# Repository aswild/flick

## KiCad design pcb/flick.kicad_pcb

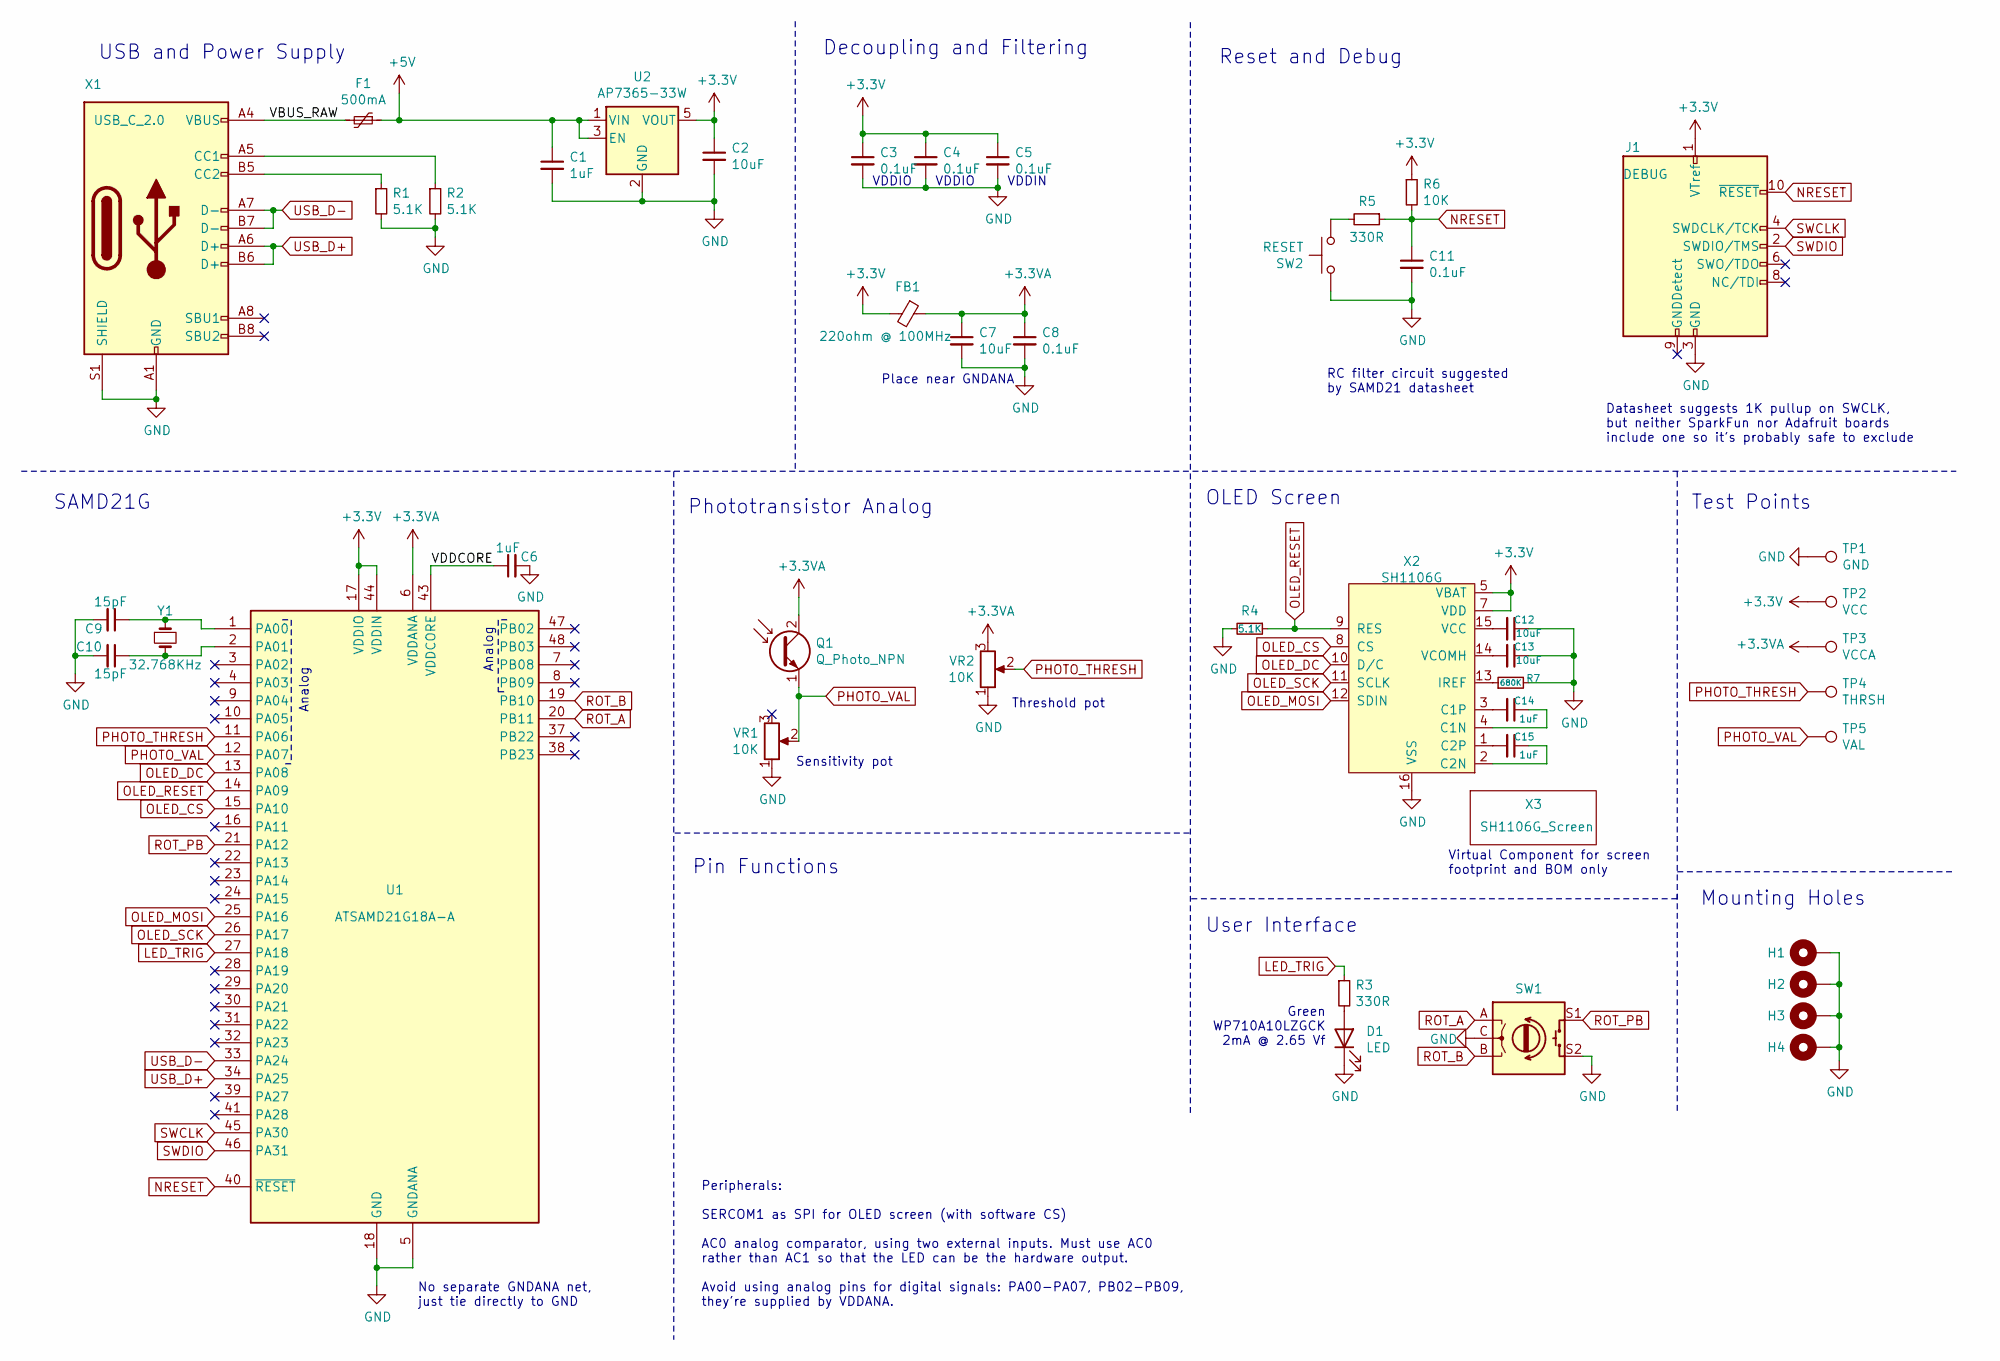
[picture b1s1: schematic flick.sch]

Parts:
C1, C6, C14, C15: 1uF; C_0805_2012Metric_Pad1.18x1.45mm_HandSolder; DigiKey PN 1276-1026-1-ND
C2, C7, C12, C13: 10uF; C_0805_2012Metric_Pad1.18x1.45mm_HandSolder; DigiKey PN 1276-2893-1-ND
C3, C4, C5, C8, C11: 0.1uF; C_0603_1608Metric_Pad1.08x0.95mm_HandSolder; DigiKey PN 1276-1935-1-ND
C9, C10: 15pF; C_0603_1608Metric_Pad1.08x0.95mm_HandSolder; DigiKey PN 1292-1487-1-ND
D1: LED; LED_D3.0mm; DigiKey PN 754-1915-ND
F1: 500mA; Fuse_1206_3216Metric_Pad1.42x1.75mm_HandSolder; DigiKey PN 507-1800-1-ND
FB1: 220ohm @ 100MHz; L_0805_2012Metric_Pad1.05x1.20mm_HandSolder; DigiKey PN A103650CT-ND
H1, H2, H3, H4: MountingHole_Pad; MountingHole_5mm_Pad
J1: DEBUG; PinHeader_2x05_P1.27mm_Vertical_SMD; DigiKey PN S9012E-05-ND
Q1: Q_Photo_NPN; LED_D5.0mm; DigiKey PN 1528-2545-ND
R1, R2, R4: 5.1K; R_0603_1608Metric_Pad0.98x0.95mm_HandSolder; DigiKey PN RMCF0603FT5K10CT-ND
R3, R5: 330R; R_0805_2012Metric_Pad1.20x1.40mm_HandSolder; DigiKey PN RMCF0805FT330RCT-ND
R6: 10K; R_0805_2012Metric_Pad1.20x1.40mm_HandSolder; DigiKey PN RMCF0805FT10K0CT-ND
R7: 680K; R_0603_1608Metric_Pad0.98x0.95mm_HandSolder; DigiKey PN RMCF0603FT680KCT-ND
SW1: Rotary_Encoder_Switch; RotaryEncoder_Bourns_PEC11L-Switch_Vertical_H20mm; DigiKey PN 118-PEC11L-4120K-S0020-ND
SW2: RESET; SW_SPST_PTS645; DigiKey PN CKN11907CT-ND
TP1: GND; TestPoint_THTPad_D1.6mm_Drill1.0mm
TP2: VCC; TestPoint_THTPad_D1.6mm_Drill1.0mm
TP3: VCCA; TestPoint_THTPad_D1.6mm_Drill1.0mm
TP4: THRSH; TestPoint_THTPad_D1.6mm_Drill1.0mm
TP5: VAL; TestPoint_THTPad_D1.6mm_Drill1.0mm
U1: ATSAMD21G18A-A; TQFP-48_7x7mm_P0.5mm; DigiKey PN ATSAMD21G18A-AFTCT-ND
U2: AP7365-33W; SOT-23-5_HandSoldering; DigiKey PN AP7365-33WG-7DICT-ND
VR1, VR2: 10K; Potentiometer_Bourns_PTV09A-1_Single_Vertical; DigiKey PN PTV09A-4020S-B103-ND
X1: USB_C_2.0; USB_C_Receptacle_GCT_USB4105; DigiKey PN 2073-USB4105-GF-ACT-ND
X2: SH1106G; GCT_FFC2B28-16_1x16-1MP_P0.5mm_Horizontal; DigiKey PN 2073-FFC2B28-16-GCT-ND
X3: SH1106G_Screen; SH1106G_SCREEN; DigiKey PN 1528-5228-ND
Y1: 32.768KHz; Crystal_SMD_MicroCrystal_CC8V-T1A-2Pin_2.0x1.2mm_HandSolder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; DigiKey PN 2195-CM8V-T1A-32.768KHZ-12.5PF-20PPM-TA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

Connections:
+3.3VA: C7.1, C8.1, FB1.1, Q1.2 (C), TP3.1, U1.6 (VDDANA), VR2.3
+3V3: C2.1, C3.1, C4.1, C5.1, FB1.2, J1.1 (VTref), R6.1, TP2.1, U1.17 (VDDIO), U1.36 (VDDIO), U1.44 (VDDIN), U2.5 (VOUT), X2.5 (VBAT), X2.7 (VDD)
+5V: C1.1, F1.1, U2.1 (VIN), U2.3 (EN)
/VBUS_RAW: F1.2, X1.A4 (VBUS), X1.A9 (VBUS), X1.B4 (VBUS), X1.B9 (VBUS)
/VDDCORE: C6.1, U1.43 (VDDCORE)
GND: C1.2, C2.2, C3.2, C4.2, C5.2, C6.2, C7.2, C8.2, C9.2, C10.2, C11.2, C12.1, C13.1, D1.1 (K), H1.1, H2.1, H3.1, H4.1, J1.3 (GND), J1.5 (GND), R1.2, R2.2, R4.2, R7.2, SW1.C, SW1.S2, SW2.1, TP1.1, U1.5 (GNDANA), U1.18 (GND), U1.35 (GND), U1.42 (GND), U2.2 (GND), VR1.1, VR2.1, X1.A1 (GND), X1.A12 (GND), X1.B1 (GND), X1.B12 (GND), X1.S1 (SHIELD), X2.6 (VSS), X2.16 (VSS)
LED_TRIG: R3.1, U1.27 (PA18)
NRESET: C11.1, J1.10 (~RESET~), R5.1, R6.2, U1.40 (~RESET)
unnamed: C9.1, U1.1 (PA00), Y1.1
unnamed: C10.1, U1.2 (PA01), Y1.2
unnamed: C12.2, X2.15 (VCC)
unnamed: C13.2, X2.14 (VCOMH)
unnamed: C14.1, X2.4 (C1N)
unnamed: C14.2, X2.3 (C1P)
unnamed: C15.1, X2.2 (C2N)
unnamed: C15.2, X2.1 (C2P)
unnamed: D1.2 (A), R3.2
unnamed: R1.1, X1.B5 (CC2)
unnamed: R2.1, X1.A5 (CC1)
unnamed: R5.2, SW2.2
unnamed: R7.1, X2.13 (IREF)
OLED_CS: U1.15 (PA10), X2.8 (CS)
OLED_DC: U1.13 (PA08), X2.10 (D/C)
OLED_MOSI: U1.25 (PA16), X2.12 (SDIN)
OLED_RESET: R4.1, U1.14 (PA09), X2.9 (RES)
OLED_SCK: U1.26 (PA17), X2.11 (SCLK)
PHOTO_THRESH: TP4.1, U1.11 (PA06), VR2.2
PHOTO_VAL: Q1.1 (E), TP5.1, U1.12 (PA07), VR1.2
ROT_A: SW1.A, U1.20 (PB11)
ROT_B: SW1.B, U1.19 (PB10)
ROT_PB: SW1.S1, U1.21 (PA12)
SWCLK: J1.4 (SWDCLK/TCK), U1.45 (PA30)
SWDIO: J1.2 (SWDIO/TMS), U1.46 (PA31)
USB_D+: U1.34 (PA25), X1.A6 (D+), X1.B6 (D+)
USB_D-: U1.33 (PA24), X1.A7 (D-), X1.B7 (D-)

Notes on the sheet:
VDDIN
VDDIO
Decoupling and Filtering
USB and Power Supply
Place near GNDANA
Phototransistor Analog
User Interface
Reset and Debug
OLED Screen
SAMD21G
Test Points
Green WP710A10LZGCK 2mA @ 2.65 Vf
Mounting Holes
Virtual Component for screen footprint and BOM only
Pin Functions
Peripherals: SERCOM1 as SPI for OLED screen (with software CS) AC0 analog comparator, using two external inputs. Must use AC0 rather than AC1 so that the LED can be the hardware output. Avoid using analog pins for digital signals: PA00-PA07, PB02-PB09, they're supplied by VDDANA.
Datasheet suggests 1K pullup on SWCLK, but neither SparkFun nor Adafruit boards include one so it's probably safe to exclude
RC filter circuit suggested by SAMD21 datasheet
Sensitivity pot
Threshold pot
No separate GNDANA net, just tie directly to GND
Analog

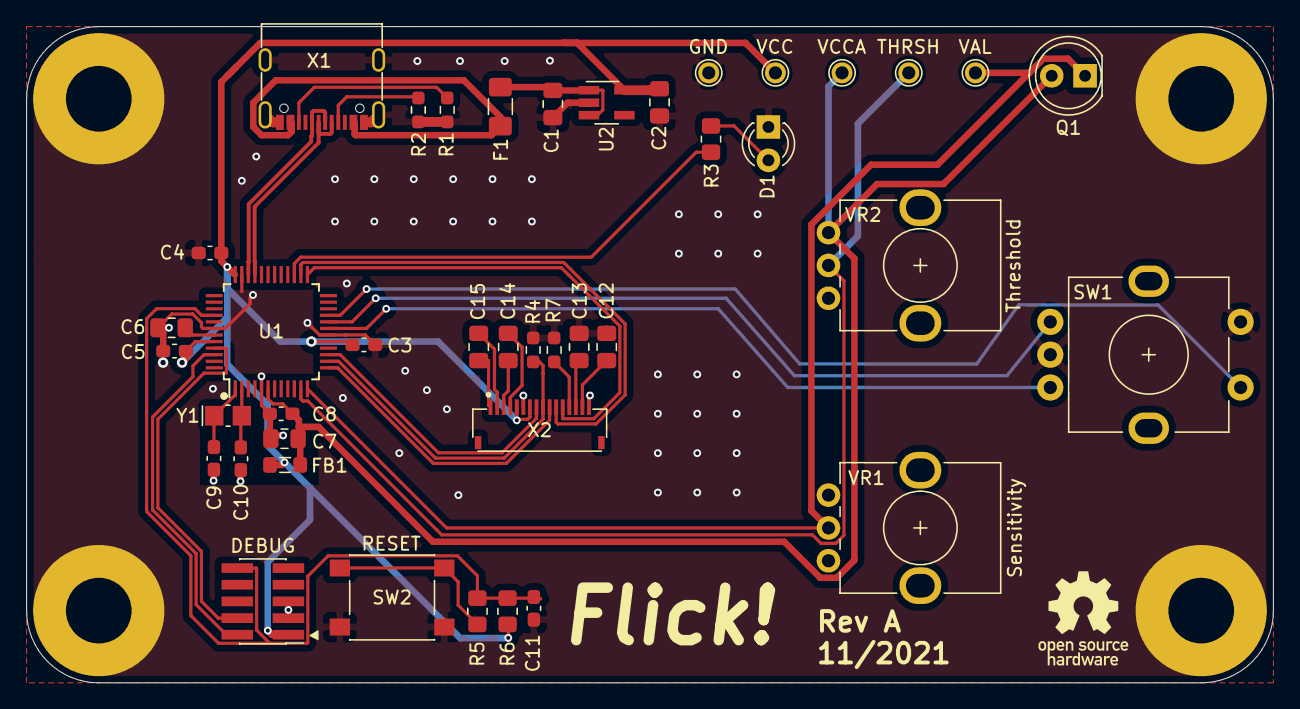
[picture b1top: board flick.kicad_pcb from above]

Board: 2 copper layers, 95.0 x 50.0 mm, 47 parts (0 on the bottom side), 35 nets.

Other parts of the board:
svg2mod: G***; Logo_OSHW_Text_7mm

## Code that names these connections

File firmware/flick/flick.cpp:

/*
 * Firmware for the Flick (rev A)
 *
 * Copyright (c) 2021 Allen Wild
 * SPDX-License-Identifier: GPL-3.0-or-later
 */

#include "Arduino.h"
#include "Adafruit_SH110X.h"
#include "RotaryEncoder.h"
#include "SPI.h"

#include "util.h"

#define LED_DIRECT_ON_AC

static Adafruit_SH1106G display(128, 64, &SPI, PIN_OLED_DC, PIN_OLED_RESET, PIN_OLED_CS);
static RotaryEncoder encoder(PIN_ROT_B, PIN_ROT_A, RotaryEncoder::LatchMode::FOUR3);

static void encoder_irq()
{
    encoder.tick();
}

void AC_Handler()
{
#ifndef LED_DIRECT_ON_AC
    if (AC->INTFLAG.bit.COMP0)
    {
        if (AC->STATUSA.bit.STATE0)
            digitalWrite(PIN_LED_TRIG, HIGH);
        else
            digitalWrite(PIN_LED_TRIG, LOW);
    }
#endif
    AC->INTFLAG.reg = AC_INTFLAG_MASK;
}

void setup()
{
    flick_init_ac();

    display.begin(0, true);
    display.display();
    delay(1000); // display splash screen

    attachInterrupt(PIN_ROT_A, encoder_irq, CHANGE);
    attachInterrupt(PIN_ROT_B, encoder_irq, CHANGE);
    setInterruptFilter(PIN_ROT_A, true);
    setInterruptFilter(PIN_ROT_B, true);

    display.setTextColor(SH110X_WHITE);
    display.setTextSize(2);

    pinMode(PIN_ROT_PB, INPUT_PULLUP);
#ifdef LED_DIRECT_ON_AC
    pinPeripheral(PIN_LED_TRIG, PIO_AC_CLK);
#else
    pinMode(PIN_LED_TRIG, OUTPUT);
#endif
}

static inline uint8_t analog_to_oled_y(int aval)
{
    return 63 - (aval >> 4);
}

void loop()
{
    static uint8_t values[128] = {0};
    static size_t pos = 0;

    int new_val = analogRead(PIN_PHOTO_VAL);
    values[pos++] = analog_to_oled_y(new_val);
    if (pos >= 128)
        pos = 0;

    int thresh = analogRead(PIN_PHOTO_THRESH);
    display.clearDisplay();
    display.writeFastHLine(0, analog_to_oled_y(thresh), 128, SH110X_WHITE);
    for (size_t i = 0; i < 128; i++)
    {
        size_t j = (i + pos) % 128;
        display.writePixel(i, values[j], SH110X_WHITE);
    }

    static int last_enc_pos = 0;
    if (!digitalRead(PIN_ROT_PB))
        encoder.setPosition(0);

    int enc_pos = encoder.getPosition();
    if (enc_pos != last_enc_pos) {
        last_enc_pos = enc_pos;
    }

    display.setCursor(0, 0);
    display.print(enc_pos);

    display.display();
    delay(100);
}

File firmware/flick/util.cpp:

/*
 * Firmware for the Flick (rev A)
 *
 * Copyright (c) 2021 Allen Wild
 * SPDX-License-Identifier: GPL-3.0-or-later
 */

#include "Arduino.h"
#include "wiring_private.h"

void flick_init_ac()
{
    // disable the AC IRQ
    NVIC_DisableIRQ(AC_IRQn);
    NVIC_ClearPendingIRQ(AC_IRQn);
    NVIC_SetPriority(AC_IRQn, 0);

    // Enable AC in power-management
    PM->APBCMASK.reg |= PM_APBCMASK_AC;

    // Set up clocks. Note: GCLK0 is 48MHz CPU clock, GCLK1 is 32.768KHz crystal clock
    while (GCLK->STATUS.bit.SYNCBUSY);
    // AC analog clock. Max 64KHz ('37.6 Maximum Clock Frequencies' Table 37-6), GCLK1 @ 32.768KHz
    GCLK->CLKCTRL.reg = GCLK_CLKCTRL_ID(GCM_AC_ANA) | GCLK_CLKCTRL_GEN_GCLK1 | GCLK_CLKCTRL_CLKEN;
    // AC digital clock, for sampling & filtering. Max 48MHz, but use GCLK1 to 'slow down' filtering
    GCLK->CLKCTRL.reg = GCLK_CLKCTRL_ID(GCM_AC_DIG) | GCLK_CLKCTRL_GEN_GCLK0 | GCLK_CLKCTRL_CLKEN;

    // wait for clock domain sync
    while (GCLK->STATUS.bit.SYNCBUSY);
    while (AC->STATUSB.bit.SYNCBUSY);

    // reset and disable AC
    AC->CTRLA.reg = AC_CTRLA_SWRST;
    while (AC->CTRLA.bit.SWRST || AC->STATUSB.bit.SYNCBUSY);
    AC->CTRLA.bit.ENABLE = 0;
    while (AC->STATUSB.bit.SYNCBUSY);

    // Configure the AC, using channel 0
    AC->CTRLA.bit.RUNSTDBY = 1;
    AC->COMPCTRL[0].reg = AC_COMPCTRL_FLEN_MAJ5     // 3/5 majority filter
                        | AC_COMPCTRL_HYST          // enable hysteresis
                        | AC_COMPCTRL_OUT_SYNC      // send synchronous (filtered) output to IO pin
                        | AC_COMPCTRL_MUXPOS_PIN3   // positive input select (PA07, PHOTO_VAL)
                        | AC_COMPCTRL_MUXNEG_PIN2   // negative input select (PA06, PHOTO_THRESH)
                        | AC_COMPCTRL_INTSEL_TOGGLE // interrupt mode (when interrupt is enabled)
                        | AC_COMPCTRL_SPEED_HIGH    // faster (and use more power)
                     // | AC_COMPCTRL_SINGLE        // single-shot mode disabled for continuous operation
                        ;

    // enable interrupt for AC 0
    AC->INTENSET.reg = AC_INTENSET_COMP0;

    // enable the AC, both the AC itself and comparator 0
    AC->CTRLA.bit.ENABLE = 1;
    AC->COMPCTRL[0].bit.ENABLE = 1;
    // sync for clock domain, and because it takes 2 digital-clock cycles for the compator to be enabled
    while (AC->STATUSB.bit.SYNCBUSY || !(AC->COMPCTRL[0].bit.ENABLE));

    // set up pinmux
    pinPeripheral(PIN_PHOTO_THRESH, PIO_ANALOG);
    pinPeripheral(PIN_PHOTO_VAL, PIO_ANALOG);

    // Enable IRQ
    NVIC_ClearPendingIRQ(AC_IRQn);
    NVIC_EnableIRQ(AC_IRQn);
}

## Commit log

2021-11-07 Initial Commit: draft schematic and pcb
2021-11-09 initial 100x60 version where I think everything works
2021-11-09 Shrink to 95x50mm part 1
    Mostly done with the routing, but there's still some power traces to
    figure out, as well as deciding what to do with various local ground
    planes (moar via stitching probably).
    * Mostly the same layout but smaller overall (to save cost at OSHPark
    which charges per square inch).
    * Remove LED driver Q2 because 7mA is actually plenty to drive an LED
2021-11-10 draft of v1 shrink complete
    Add test points, flip the phototransistor footprint around (so
    anode/cathode is consistent with standard LEDs), finish routing power
    and stuff.
    TODO: Add silkscreen text/graphics, verify I can actually order
    everything in the BOM, double-check everything before production.
2021-11-11 Flick v1 PCB Rev A Final
    Here we go, I'm gonna send this to OSH Park and hope it works. Minor
    layout tweaks, add silkscreen decorations, and double-check everything.
2021-11-11 Add spreadsheet of IO pin functions
    Screenshotted to add to the schematic, since Eeschema doesn't have
    a built-in way to add text tables.
2021-11-21 pcb: update 3D models to avoid absolute paths
    Add "Wild" as a 3D Search Paths alias in the Configure Paths dialog of
    Footprint Editor that points to the kicad-libraries-wild/3d folder, that
    way I don't have to worry about hard-coded aboslute paths.
    Warning: kicad saves files as CRLF on Windows, so dos2unix all the
    things before committing to avoid a 100% git diff. It also seems to
    re-sort a lot of the data so I manually only accepted part of the diff
2021-11-24 firmware: import from samd21 rev 50f59b4efe45c2314a5b9365317e7b54dff0e731
    Squash-merge from https://github.com/aswild/samd21 into the firmware
    directory. Since I'll be making deeper board variant changes for Flick,
    it makes more sense to keep the firmware code here rather than my usual
    samd21 monorepo.
    This is a manual squash-merge rather than git subtree so that I can
    remove the unneeded sketches and libraries without having them clutter
2021-11-24 firmware: rewrite variant files for Flick
    Replace g_APinDescription with a stripped down pin list for Flick rev A,
    and define PIN_ names for all functions that match what they're called
    in the schematic and Pin_Functions spreadsheet.
2021-11-24 firmware: delete unused Adafruit graphics/display files
    less clutter, less code to compile.
2021-11-24 firmware/bootloader: update for Flick's LED pin
    The SparkFun SAMD21 Mini board has 3 LEDs (general plus separate RX/TX)
    but Flick currently only has one.
2021-11-24 firmware: add "flick" sketch, skeleton for the main firmware user code
    Currently just a test program to demo the hardware
2021-11-24 firmware: remove I2C (Wire) entirely
    Don't need I2C for Flick, so there's no need to keep that library code
    around.
    I had to do heavy modifications to the Adafruit graphics and BusIO
    libraries to remove all references to the I2C/Wire APIs. It's not the
    prettiest code, but the compiled binary is a few kB smaller and there's
    fewer runtime "spi or i2c" runtime checks in the OLED code now.
2021-11-26 firmware: get the AC working and test PHOTO_THRESH
    Yay it works, but its potentiometer is also backwards, as expected.
    Change the test code into a basic graph display. Also hook up the LED to
    the AC IRQ, but PWM it at 5% rather than driving at full strength
    because this LED is too dang bright. (Proper fix is to solder
    a different resistor to the board, but using PWM outputs is easy enough
    cheating)
2021-11-28 firmare: add new splash logo image and script to convert it
    Splash logo is just text from Photoshop right now, but it'll work for
    testing. Adafruit_GFX doesn't ship tools to convert images to its
    bit-packed bitmap format, so I wrote my own in Python using PIL.
2021-11-28 firmware: add "logo" splash screen
    Just replace the Adafruit logo to avoid having unnecessary splash
    bitmaps in the code.
    Also tweak img2gfxbitmap so it doesn't produce trailing whitespace
2021-11-29 firmware: include wiring_private from Arduino.h
    Just always make pinPeripheral available, I use it manually a lot rather
    than reserving that ability for libraries.
2021-11-29 firmware: remove PWM stuff from demo code
    Now that I have a bigger resistor (2.2k rather than 330) that doesn't
    blind me at full brightness, I can drop the PWM stuff and just drive the
    LED as a normal GPIO, or optionally drive it directly from the AC
    peripheral.
    Also switch the AC digital clock from the 32.768k crystal to 48MHz from
    the CPU to minimize its latency. In the future I might derive a ~1MHz
2021-11-29 pcb: add notes on board errata
    So I know what to fix when the time comes for Rev B.
2021-11-29 firmware: import UF2 bootloader
    Import rev dd415d582b3179a6d752d0ce50da3247411aa6e8 of
    https://github.com/Microsoft/uf2-samdx1
    Delete the duplicate copies of CMSIS and Atmel sam headers, I'll be
    using the common versions (which are newer than what's in the upstream
    repo anyway)
2021-11-29 firmware: update UF2 bootloader for Flick
    Rewrite the Makefile entirely (based on my previous SAM-BA bootloader
    Makefile), make it compile with -Wextra, define a board variant for
    Flick, and do some code tweaks.
    * change INDEX_URL to point to the flick repo
    * disable HID and WebUSB
    * change double tap magic (DBL_TAP_MAGIC) value to match my firmware
2021-11-29 firmware: add uf2conv script
    From rev a690c5a4d9abe393496b3ade88489d39da07b458 of
    https://github.com/microsoft/uf2
2021-11-29 firmware: build UF2 binary
    And 'make uploaduf2' to program it to /run/media/$(USER)/FLICK (which
    works on my linux box, but might need more complex logic to find
    UF2_DRIVE_PATH)
2021-11-29 firmware: uf2 bootloader: remove python2 dependency, fix upload-bossa
    'make upload-bossa' now always programs the self-update version, using
    the correct flags to program to offset 0x2000.
    Update gendata.py to work with python3, all I had to change was '/'
    operators to '//' to get integer division (all the existing IO and
    bytearray code was fine), and allow parsing the bootloader size as hex.
2021-11-29 firmware: fix deprecated openocd.cfg option
    Fixes "DEPRECATED! use 'adapter driver' not 'interface'" when starting
    openocd.
2021-12-22 add skeleton for flick-flasher, the PC software component
    I've decided to do this in Rust using the pixels library to get
    a GPU-accelerated framebuffer, and winit to handle windowing.
    Pixels is a simple bitmap framebuffer, but it uses GPU acceleration to
    render and display via wgpu. That said, all my "rendering" is
    a CPU-bound loop operating on a byte slice, but the display logic is
    simple. It also supports toggling vsync, which could be helpful.
2022-01-01 flasher: rewrite for Flick instead of the pixels example
    I also optimized the hell out of it by minimizing the framebuffer size,
    which had a much bigger effect than making a fancy unsafe int fill
    function.
2022-01-01 flasher: remove the fast optimized draw function
    I had a good time looking at "cargo asm" and reasoning about unsafe code
    to write this optimized implementation that LLVM can aggressively
    vectorize and unroll. It's not actually needed, but I want to have it
    committed for posterity's sake.
2022-01-02 flasher: add back env_logger
    wgpu logs quite a bit, and those logs are actually quite helpful for
    diagnosing issues, such as when the program unexpectedly crashes on
    startup on Windows.
2022-01-02 flasher: add workaround for integrated vs discrete GPU adapter selection
    When I tried to run it on my desktop on Windows, wgpu decided to try to
    use the integrated graphics rather than my actual GPU. Maybe "Intel"
    gets sorted before "Nvidia"?
    Anyway, this is a total hack but apparently requesting an adapter with
    a preference for HighPerformance causes wgpu to correctly pick the
    proper GPU.
2022-01-30 firmware: remove extraneous executable mode on files
